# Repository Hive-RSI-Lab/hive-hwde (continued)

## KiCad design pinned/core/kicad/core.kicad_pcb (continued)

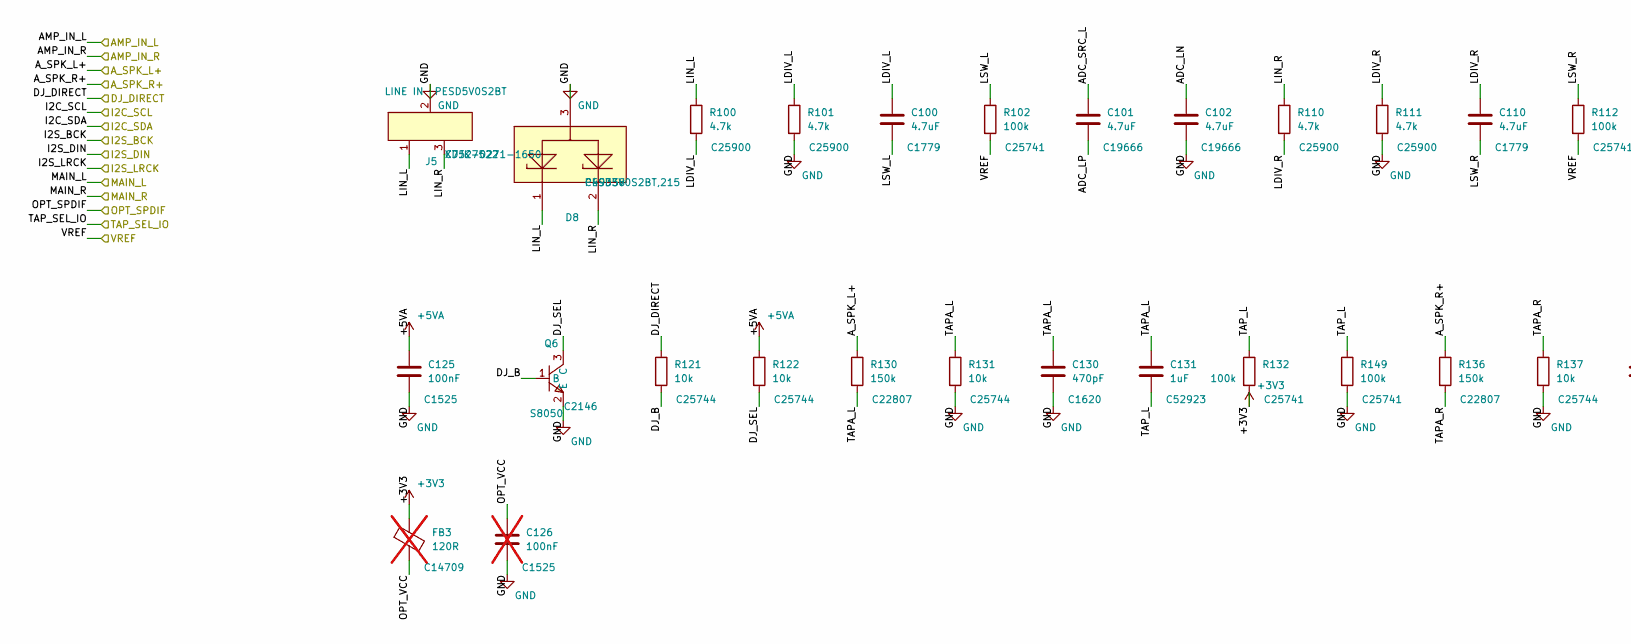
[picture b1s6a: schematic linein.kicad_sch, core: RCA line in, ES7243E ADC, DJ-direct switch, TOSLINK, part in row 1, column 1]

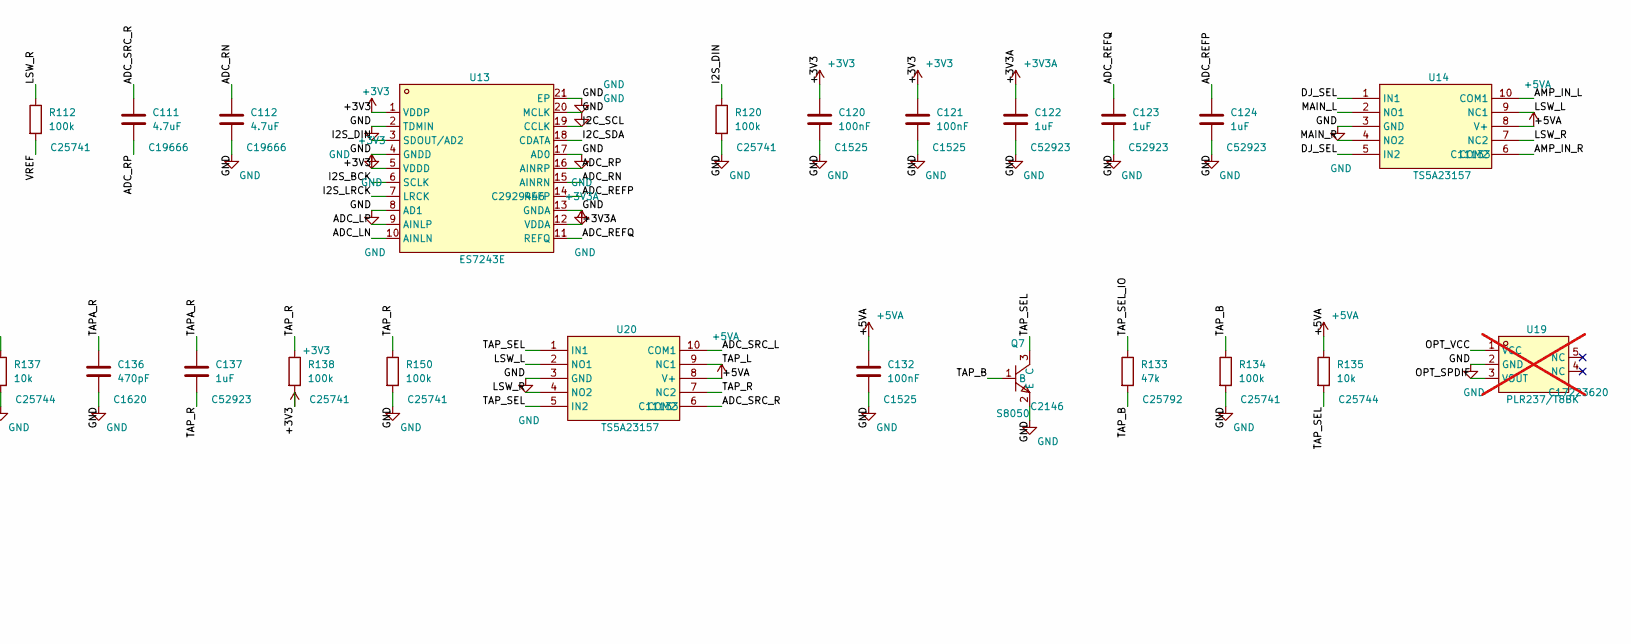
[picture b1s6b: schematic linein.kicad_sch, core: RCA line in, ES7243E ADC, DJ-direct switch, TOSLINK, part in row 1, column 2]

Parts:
C100, C110: 4.7uF; C0805; LCSC C1779
C101, C102, C111, C112: 4.7uF; C0603; LCSC C19666
C120, C121, C125, C132: 100nF; C0402; LCSC C1525
C122, C123, C124, C131, C137: 1uF; C0402; LCSC C52923
C126: 100nF; C0402; LCSC C1525; not fitted
C130, C136: 470pF; C0603; LCSC C1620
D8: PESD5V0S2BT; SOT-23_L2.9-W1.3-P1.90-LS2.4-BR; MPN PESD5V0S2BT,215; LCSC C49338
FB3: 120R; L0603; LCSC C14709; not fitted
J5: LINE IN; CONN-TH_XDJK-0271-1650; MPN XDJK-0271-1650; LCSC C7527522
Q6, Q7: S8050; SOT-23-3_L3.0-W1.7-P0.95-LS2.9-BR; LCSC C2146
R100, R101, R110, R111: 4.7k; R0402; LCSC C25900
R102, R112, R120, R132, R134, R138, R149, R150: 100k; R0402; LCSC C25741
R121, R122, R131, R135, R137: 10k; R0402; LCSC C25744
R130, R136: 150k; R0603; LCSC C22807
R133: 47k; R0402; LCSC C25792
U13: ES7243E; QFN-20_L3.0-W3.0-P0.40-BL-EP1.7; LCSC C2929446
U14, U20: TS5A23157; MSOP-10_L3.0-W3.0-P0.50-LS5.0-BL; LCSC C11133
U19: PLR237/T8BK; OPTO-TH_PLR237-T10BK; LCSC C17223620; not fitted

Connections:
+3V3: C120.1, C121.1, FB3.1, R132.2, R138.2, U13.1 (VDDP), U13.5 (VDDD); also elsewhere on the board
+3V3A: C122.1, U13.12 (VDDA); also elsewhere on the board
+5VA: C125.1, C132.1, R122.1, R135.1, U14.8 (V+), U20.8 (V+); also elsewhere on the board
/AMP_IN_L: U14.10 (COM1); also elsewhere on the board
/AMP_IN_R: U14.6 (COM2); also elsewhere on the board
/A_SPK_L+: R130.1; also elsewhere on the board
/A_SPK_R+: R136.1; also elsewhere on the board
/DJ_DIRECT: R121.1; also elsewhere on the board
/I2C_SCL: U13.19 (CCLK); also elsewhere on the board
/I2C_SDA: U13.18 (CDATA); also elsewhere on the board
/I2S_BCK: U13.6 (SCLK); also elsewhere on the board
/I2S_DIN: R120.1, U13.3 (SDOUT/AD2); also elsewhere on the board
/I2S_LRCK: U13.7 (LRCK); also elsewhere on the board
/MAIN_L: U14.2 (NO1); also elsewhere on the board
/MAIN_R: U14.4 (NO2); also elsewhere on the board
/OPT_SPDIF: U19.3 (VOUT); also elsewhere on the board
/TAP_SEL_IO: R133.1; also elsewhere on the board
/VREF: R102.2, R112.2; also elsewhere on the board
/linein/ADC_LN: C102.1, U13.10 (AINLN)
/linein/ADC_LP: C101.2, U13.9 (AINLP)
/linein/ADC_REFP: C124.1, U13.14 (REFP)
/linein/ADC_REFQ: C123.1, U13.11 (REFQ)
/linein/ADC_RN: C112.1, U13.15 (AINRN)
/linein/ADC_RP: C111.2, U13.16 (AINRP)
/linein/ADC_SRC_L: C101.1, U20.10 (COM1)
/linein/ADC_SRC_R: C111.1, U20.6 (COM2)
/linein/DJ_B: Q6.1 (B), R121.2
/linein/DJ_SEL: Q6.3 (C), R122.2, U14.1 (IN1), U14.5 (IN2)
/linein/LDIV_L: C100.1, R100.2, R101.1
/linein/LDIV_R: C110.1, R110.2, R111.1
/linein/LIN_L: D8.1, J5.1, R100.1
/linein/LIN_R: D8.2, J5.3, R110.1
/linein/LSW_L: C100.2, R102.1, U14.9 (NC1), U20.2 (NO1)
/linein/LSW_R: C110.2, R112.1, U14.7 (NC2), U20.4 (NO2)
/linein/OPT_VCC: C126.1, FB3.2, U19.1 (VCC)
/linein/TAPA_L: C130.1, C131.1, R130.2, R131.1
/linein/TAPA_R: C136.1, C137.1, R136.2, R137.1
/linein/TAP_B: Q7.1 (B), R133.2, R134.1
/linein/TAP_L: C131.2, R132.1, R149.1, U20.9 (NC1)
/linein/TAP_R: C137.2, R138.1, R150.1, U20.7 (NC2)
/linein/TAP_SEL: Q7.3 (C), R135.2, U20.1 (IN1), U20.5 (IN2)
GND: C102.2, C112.2, C120.2, C121.2, C122.2, C123.2, C124.2, C125.2, C126.2, C130.2, C132.2, C136.2, D8.3, J5.2, Q6.2 (E), Q7.2 (E), R101.2, R111.2, R120.2, R131.2, R134.2, R137.2, R149.2, R150.2, U13.2 (TDMIN), U13.4 (GNDD), U13.8 (AD1), U13.13 (GNDA), U13.17 (AD0), U13.20 (MCLK), U13.21 (EP), U14.3 (GND), U19.2 (GND), U20.3 (GND); also elsewhere on the board

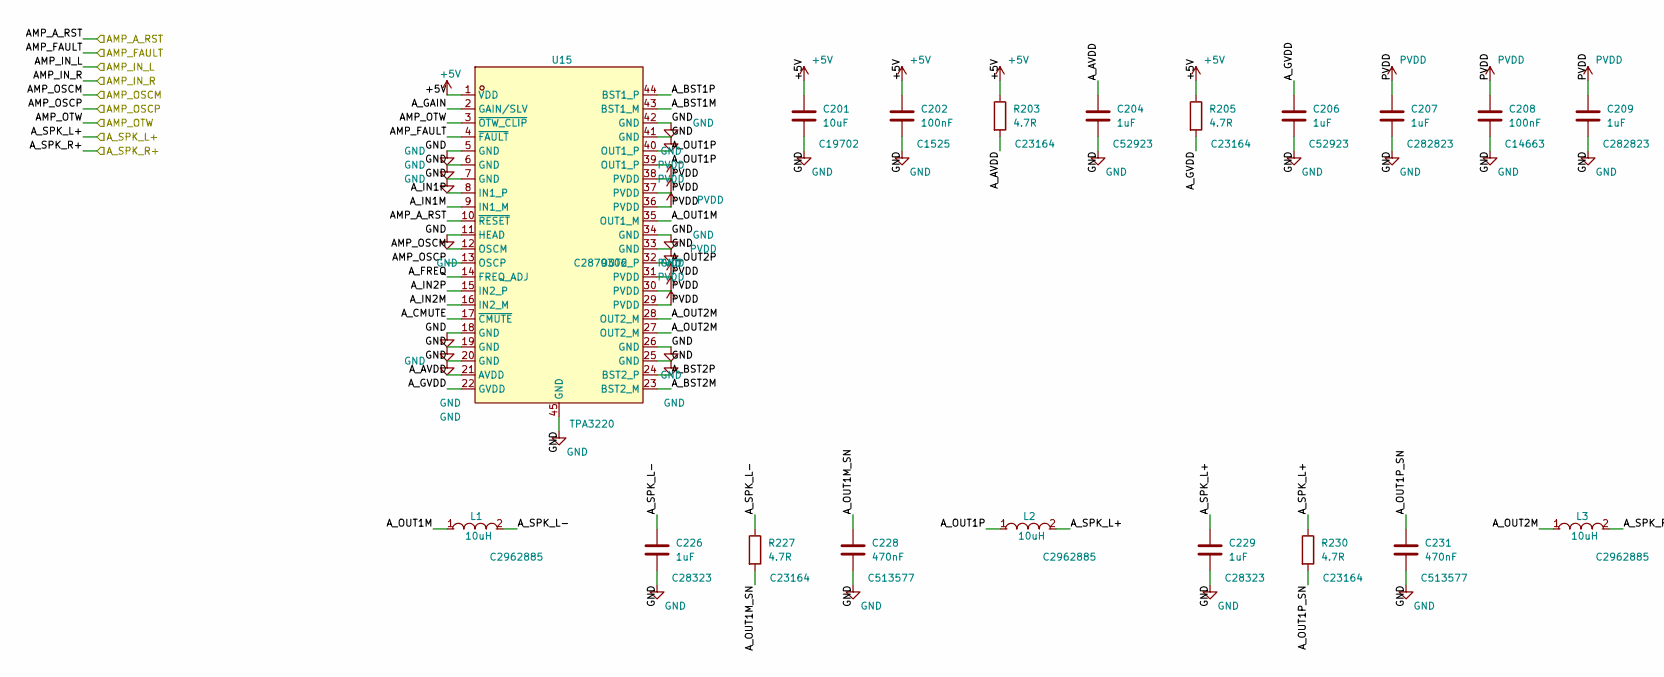
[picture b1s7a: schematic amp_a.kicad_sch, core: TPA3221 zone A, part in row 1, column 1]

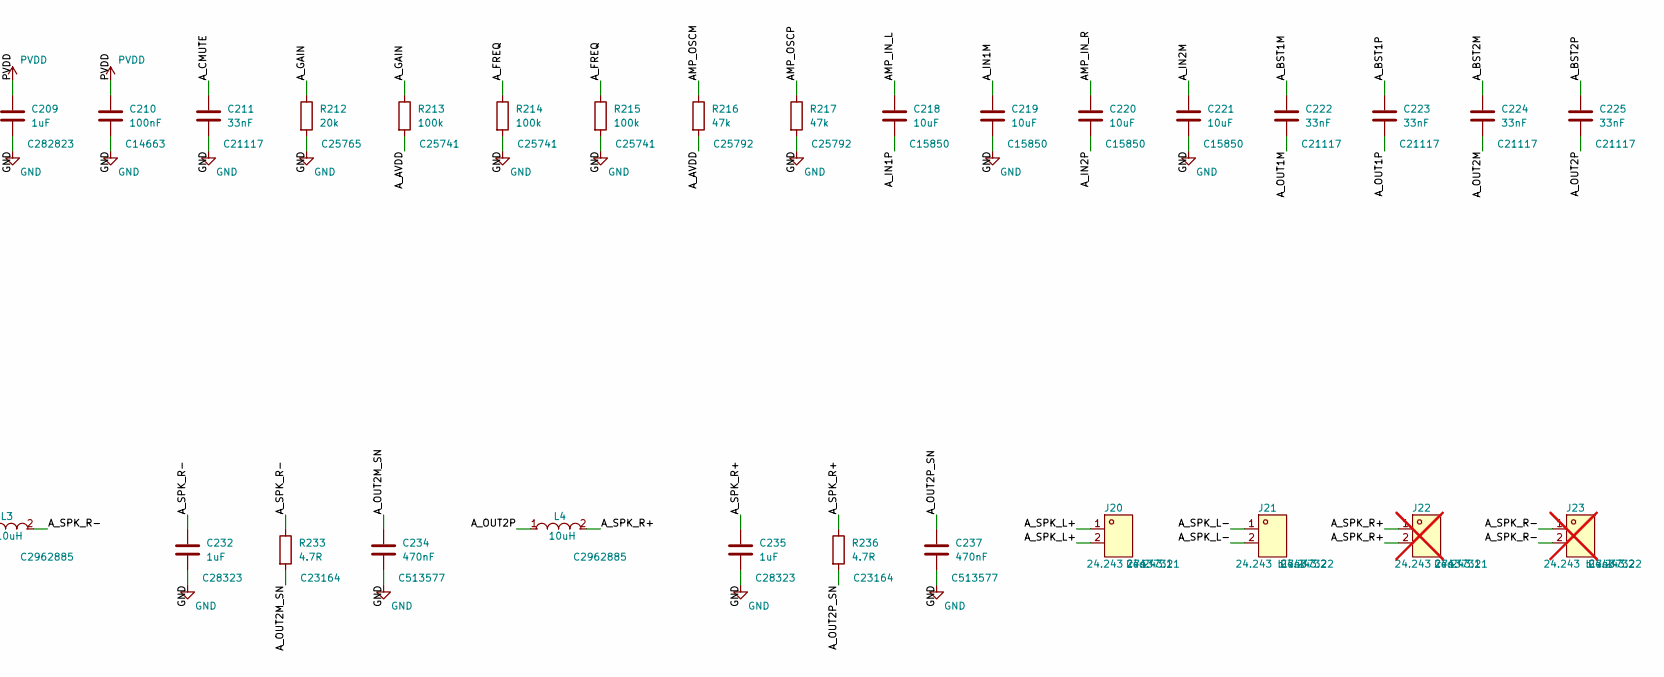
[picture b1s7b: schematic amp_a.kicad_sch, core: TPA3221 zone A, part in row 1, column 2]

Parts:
C201: 10uF; C0603; LCSC C19702
C202: 100nF; C0402; LCSC C1525
C204, C206: 1uF; C0402; LCSC C52923
C207, C209: 1uF; C1206; LCSC C282823
C208, C210: 100nF; C0603; LCSC C14663
C211, C222, C223, C224, C225: 33nF; C0603; LCSC C21117
C218, C219, C220, C221: 10uF; C0805; LCSC C15850
C226, C229, C232, C235: 1uF; C0805; LCSC C28323
C228, C231, C234, C237: 470nF; C0603; LCSC C513577
J20: 24.243 red; CONN-TH_24.243.1_RED; MPN 24.243.1; LCSC C7437321
J21: 24.243 black; CONN-TH_24.243.2; MPN 24.243.2; LCSC C7437322
J22: 24.243 red; CONN-TH_24.243.1_RED; MPN 24.243.1; LCSC C7437321; not fitted
J23: 24.243 black; CONN-TH_24.243.2; MPN 24.243.2; LCSC C7437322; not fitted
L1, L2, L3, L4: 10uH; IND-SMD_L8.5-W8.0_PCC-M0854M; LCSC C2962885
R203, R205, R227, R230, R233, R236: 4.7R; R0603; LCSC C23164
R212: 20k; R0402; LCSC C25765
R213, R214, R215: 100k; R0402; LCSC C25741
R216, R217: 47k; R0402; LCSC C25792
U15: TPA3220; HTSSOP-44-1EP_L14.0-W6.1-P0.64-LS8.1-EP7.3x4.43; LCSC C2879306

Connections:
+5V: C201.1, C202.1, R203.1, R205.1, U15.1 (VDD); also elsewhere on the board
/AMP_A_RST: U15.10 (~RESET); also elsewhere on the board
/AMP_FAULT: U15.4 (~FAULT); also elsewhere on the board
/AMP_IN_L: C218.1; also elsewhere on the board
/AMP_IN_R: C220.1; also elsewhere on the board
/AMP_OSCM: R216.1, U15.12 (OSCM); also elsewhere on the board
/AMP_OSCP: R217.1, U15.13 (OSCP); also elsewhere on the board
/AMP_OTW: U15.3 (~OTW_CLIP); also elsewhere on the board
/A_SPK_L+: C229.1, J20.1, J20.2, L2.2, R230.1; also elsewhere on the board
/A_SPK_R+: C235.1, J22.1, J22.2, L4.2, R236.1; also elsewhere on the board
/amp_a/A_AVDD: C204.1, R203.2, R213.2, R216.2, U15.21 (AVDD)
/amp_a/A_BST1M: C222.1, U15.43 (BST1_M)
/amp_a/A_BST1P: C223.1, U15.44 (BST1_P)
/amp_a/A_BST2M: C224.1, U15.23 (BST2_M)
/amp_a/A_BST2P: C225.1, U15.24 (BST2_P)
/amp_a/A_CMUTE: C211.1, U15.17 (~CMUTE)
/amp_a/A_FREQ: R214.1, R215.1, U15.14 (FREQ_ADJ)
/amp_a/A_GAIN: R212.1, R213.1, U15.2 (GAIN/SLV)
/amp_a/A_GVDD: C206.1, R205.2, U15.22 (GVDD)
/amp_a/A_IN1M: C219.1, U15.9 (IN1_M)
/amp_a/A_IN1P: C218.2, U15.8 (IN1_P)
/amp_a/A_IN2M: C221.1, U15.16 (IN2_M)
/amp_a/A_IN2P: C220.2, U15.15 (IN2_P)
/amp_a/A_OUT1M: C222.2, L1.1, U15.35 (OUT1_M)
/amp_a/A_OUT1M_SN: C228.1, R227.2
/amp_a/A_OUT1P: C223.2, L2.1, U15.39 (OUT1_P), U15.40 (OUT1_P)
/amp_a/A_OUT1P_SN: C231.1, R230.2
/amp_a/A_OUT2M: C224.2, L3.1, U15.27 (OUT2_M), U15.28 (OUT2_M)
/amp_a/A_OUT2M_SN: C234.1, R233.2
/amp_a/A_OUT2P: C225.2, L4.1, U15.32 (OUT2_P)
/amp_a/A_OUT2P_SN: C237.1, R236.2
/amp_a/A_SPK_L-: C226.1, J21.1, J21.2, L1.2, R227.1
/amp_a/A_SPK_R-: C232.1, J23.1, J23.2, L3.2, R233.1
GND: C201.2, C202.2, C204.2, C206.2, C207.2, C208.2, C209.2, C210.2, C211.2, C219.2, C221.2, C226.2, C228.2, C229.2, C231.2, C232.2, C234.2, C235.2, C237.2, R212.2, R214.2, R215.2, R217.2, U15.5 (GND), U15.6 (GND), U15.7 (GND), U15.11 (HEAD), U15.18 (GND), U15.19 (GND), U15.20 (GND), U15.25 (GND), U15.26 (GND), U15.33 (GND), U15.34 (GND), U15.41 (GND), U15.42 (GND), U15.45 (GND); also elsewhere on the board
PVDD: C207.1, C208.1, C209.1, C210.1, U15.29 (PVDD), U15.30 (PVDD), U15.31 (PVDD), U15.36 (PVDD), U15.37 (PVDD), U15.38 (PVDD); also elsewhere on the board

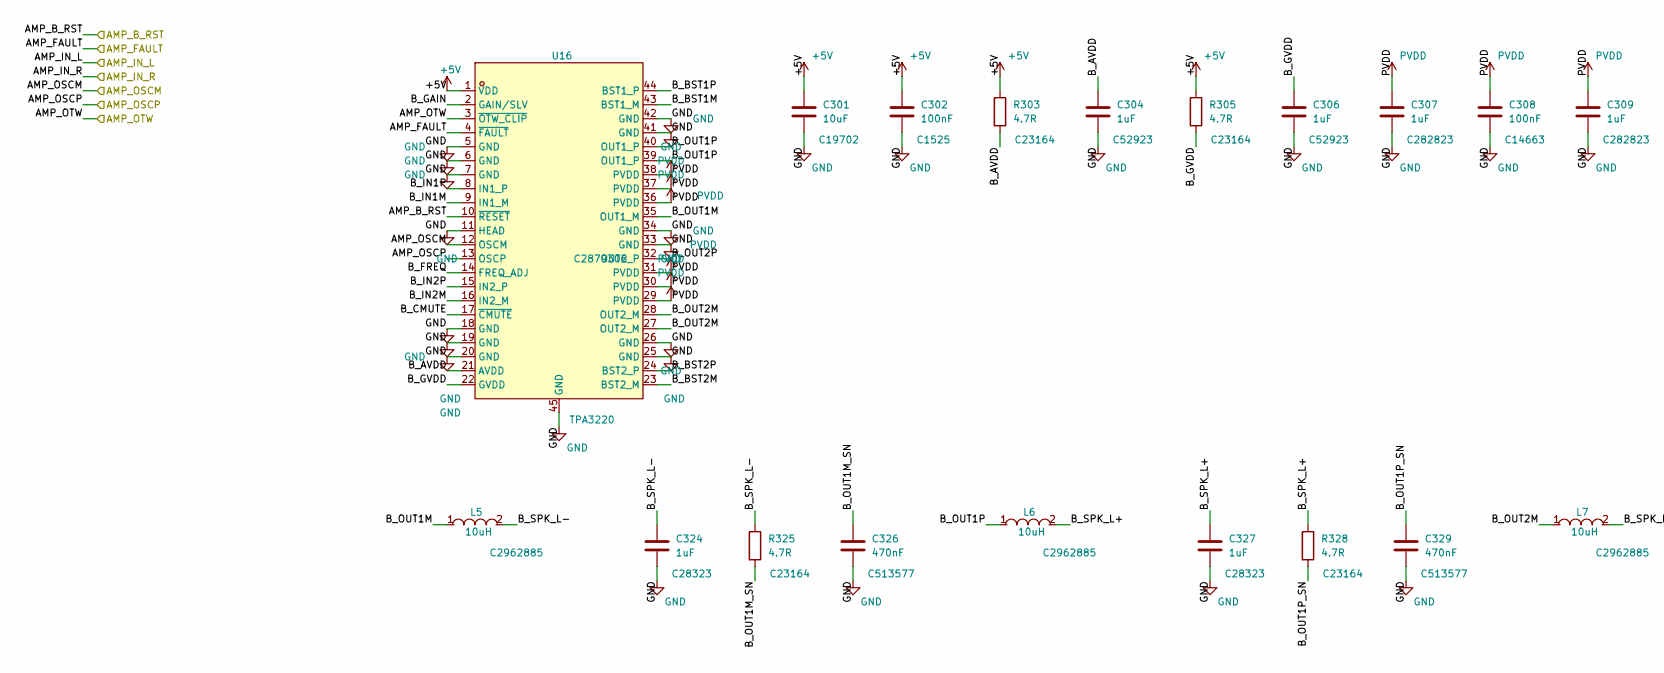
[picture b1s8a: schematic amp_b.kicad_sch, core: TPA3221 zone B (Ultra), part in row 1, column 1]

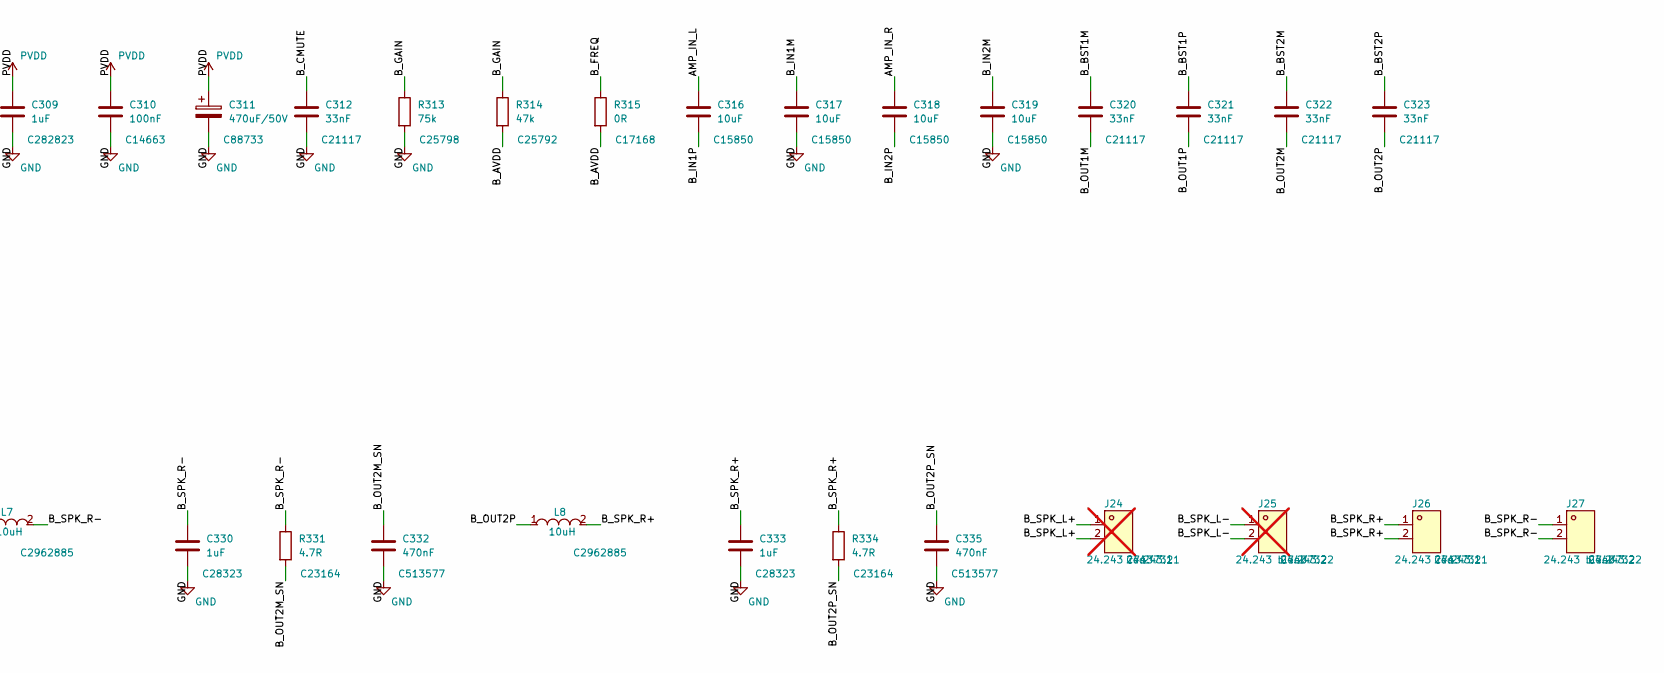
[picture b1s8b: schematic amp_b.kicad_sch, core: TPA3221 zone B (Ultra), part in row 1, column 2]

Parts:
C301: 10uF; C0603; LCSC C19702
C302: 100nF; C0402; LCSC C1525
C304, C306: 1uF; C0402; LCSC C52923
C307, C309: 1uF; C1206; LCSC C282823
C308, C310: 100nF; C0603; LCSC C14663
C311: 470uF/50V; CAP-TH_BD10.0-P5.00-D1.0-FD; LCSC C88733
C312, C320, C321, C322, C323: 33nF; C0603; LCSC C21117
C316, C317, C318, C319: 10uF; C0805; LCSC C15850
C324, C327, C330, C333: 1uF; C0805; LCSC C28323
C326, C329, C332, C335: 470nF; C0603; LCSC C513577
J24: 24.243 red; CONN-TH_24.243.1_RED; MPN 24.243.1; LCSC C7437321; not fitted
J25: 24.243 black; CONN-TH_24.243.2; MPN 24.243.2; LCSC C7437322; not fitted
J26: 24.243 red; CONN-TH_24.243.1_RED; MPN 24.243.1; LCSC C7437321
J27: 24.243 black; CONN-TH_24.243.2; MPN 24.243.2; LCSC C7437322
L5, L6, L7, L8: 10uH; IND-SMD_L8.5-W8.0_PCC-M0854M; LCSC C2962885
R303, R305, R325, R328, R331, R334: 4.7R; R0603; LCSC C23164
R313: 75k; R0402; LCSC C25798
R314: 47k; R0402; LCSC C25792
R315: 0R; R0402; LCSC C17168
U16: TPA3220; HTSSOP-44-1EP_L14.0-W6.1-P0.64-LS8.1-EP7.3x4.43; LCSC C2879306

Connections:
+5V: C301.1, C302.1, R303.1, R305.1, U16.1 (VDD); also elsewhere on the board
/AMP_B_RST: U16.10 (~RESET); also elsewhere on the board
/AMP_FAULT: U16.4 (~FAULT); also elsewhere on the board
/AMP_IN_L: C316.1; also elsewhere on the board
/AMP_IN_R: C318.1; also elsewhere on the board
/AMP_OSCM: U16.12 (OSCM); also elsewhere on the board
/AMP_OSCP: U16.13 (OSCP); also elsewhere on the board
/AMP_OTW: U16.3 (~OTW_CLIP); also elsewhere on the board
/amp_b/B_AVDD: C304.1, R303.2, R314.2, R315.2, U16.21 (AVDD)
/amp_b/B_BST1M: C320.1, U16.43 (BST1_M)
/amp_b/B_BST1P: C321.1, U16.44 (BST1_P)
/amp_b/B_BST2M: C322.1, U16.23 (BST2_M)
/amp_b/B_BST2P: C323.1, U16.24 (BST2_P)
/amp_b/B_CMUTE: C312.1, U16.17 (~CMUTE)
/amp_b/B_FREQ: R315.1, U16.14 (FREQ_ADJ)
/amp_b/B_GAIN: R313.1, R314.1, U16.2 (GAIN/SLV)
/amp_b/B_GVDD: C306.1, R305.2, U16.22 (GVDD)
/amp_b/B_IN1M: C317.1, U16.9 (IN1_M)
/amp_b/B_IN1P: C316.2, U16.8 (IN1_P)
/amp_b/B_IN2M: C319.1, U16.16 (IN2_M)
/amp_b/B_IN2P: C318.2, U16.15 (IN2_P)
/amp_b/B_OUT1M: C320.2, L5.1, U16.35 (OUT1_M)
/amp_b/B_OUT1M_SN: C326.1, R325.2
/amp_b/B_OUT1P: C321.2, L6.1, U16.39 (OUT1_P), U16.40 (OUT1_P)
/amp_b/B_OUT1P_SN: C329.1, R328.2
/amp_b/B_OUT2M: C322.2, L7.1, U16.27 (OUT2_M), U16.28 (OUT2_M)
/amp_b/B_OUT2M_SN: C332.1, R331.2
/amp_b/B_OUT2P: C323.2, L8.1, U16.32 (OUT2_P)
/amp_b/B_OUT2P_SN: C335.1, R334.2
/amp_b/B_SPK_L+: C327.1, J24.1, J24.2, L6.2, R328.1
/amp_b/B_SPK_L-: C324.1, J25.1, J25.2, L5.2, R325.1
/amp_b/B_SPK_R+: C333.1, J26.1, J26.2, L8.2, R334.1
/amp_b/B_SPK_R-: C330.1, J27.1, J27.2, L7.2, R331.1
GND: C301.2, C302.2, C304.2, C306.2, C307.2, C308.2, C309.2, C310.2, C311.2, C312.2, C317.2, C319.2, C324.2, C326.2, C327.2, C329.2, C330.2, C332.2, C333.2, C335.2, R313.2, U16.5 (GND), U16.6 (GND), U16.7 (GND), U16.11 (HEAD), U16.18 (GND), U16.19 (GND), U16.20 (GND), U16.25 (GND), U16.26 (GND), U16.33 (GND), U16.34 (GND), U16.41 (GND), U16.42 (GND), U16.45 (GND); also elsewhere on the board
PVDD: C307.1, C308.1, C309.1, C310.1, C311.1, U16.29 (PVDD), U16.30 (PVDD), U16.31 (PVDD), U16.36 (PVDD), U16.37 (PVDD), U16.38 (PVDD); also elsewhere on the board

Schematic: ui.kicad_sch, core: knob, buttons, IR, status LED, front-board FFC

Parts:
C400: 4.7uF; C0603; LCSC C19666
D3: KT-0603R; LED-SMD_L1.6-W0.8-R-RD; LCSC C2286
J3: FFC 20P; FPC-SMD_20P-P0.50_XUNPU_FPC-05F-20PH20; LCSC C2856803; not fitted
R400: 100R; R0402; LCSC C25076
R401: 470R; R0402; LCSC C25117
R402, R403: 33R; R0402; LCSC C25105; not fitted
SW1: EC11; SW-TH_EC11E1820402; LCSC C361165
SW2: BTN1; SW-SMD_4P-L5.1-W5.1-P3.70-LS6.5-TL_H1.5; MPN TS-1187A-B-A-B; LCSC C318884
SW3: BTN2; SW-SMD_4P-L5.1-W5.1-P3.70-LS6.5-TL_H1.5; MPN TS-1187A-B-A-B; LCSC C318884
U18: IRM-3638T; OPTO-TH_IRM-3638T; LCSC C42421366

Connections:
+3V3: J3.2, J3.19, R400.1; also elsewhere on the board
+5V: J3.3, J3.18; also elsewhere on the board
/BTN_1: SW2.1 (A), SW2.2 (B); also elsewhere on the board
/BTN_2: SW3.1 (A), SW3.2 (B); also elsewhere on the board
/ENC_A: J3.16, SW1.A; also elsewhere on the board
/ENC_B: J3.17, SW1.B; also elsewhere on the board
/ENC_SW: SW1.D; also elsewhere on the board
/EXP_INT: J3.14; also elsewhere on the board
/I2C_SCL: J3.12; also elsewhere on the board
/I2C_SDA: J3.13; also elsewhere on the board
/IR_IN: J3.15, U18.1 (OUT); also elsewhere on the board
/LCD_BL: J3.10; also elsewhere on the board
/LCD_CS: J3.8; also elsewhere on the board
/LCD_DC: J3.9; also elsewhere on the board
/LCD_MOSI: R403.1; also elsewhere on the board
/LCD_SCLK: R402.1; also elsewhere on the board
/LED_STATUS: R401.1; also elsewhere on the board
/ui/FFC_MOSI: J3.7, R403.2
/ui/FFC_SCK: J3.5, R402.2
/ui/IR_VCC: C400.1, R400.2, U18.3 (VCC)
/ui/LED_A: D3.1 (A), R401.2
GND: C400.2, D3.2 (K), J3.1, J3.4, J3.6, J3.11, J3.20, J3.21, J3.22, SW1.C, SW1.E, SW1.F, SW1.G, SW2.3 (C), SW2.4 (D), SW3.3 (C), SW3.4 (D), U18.2 (GND); also elsewhere on the board

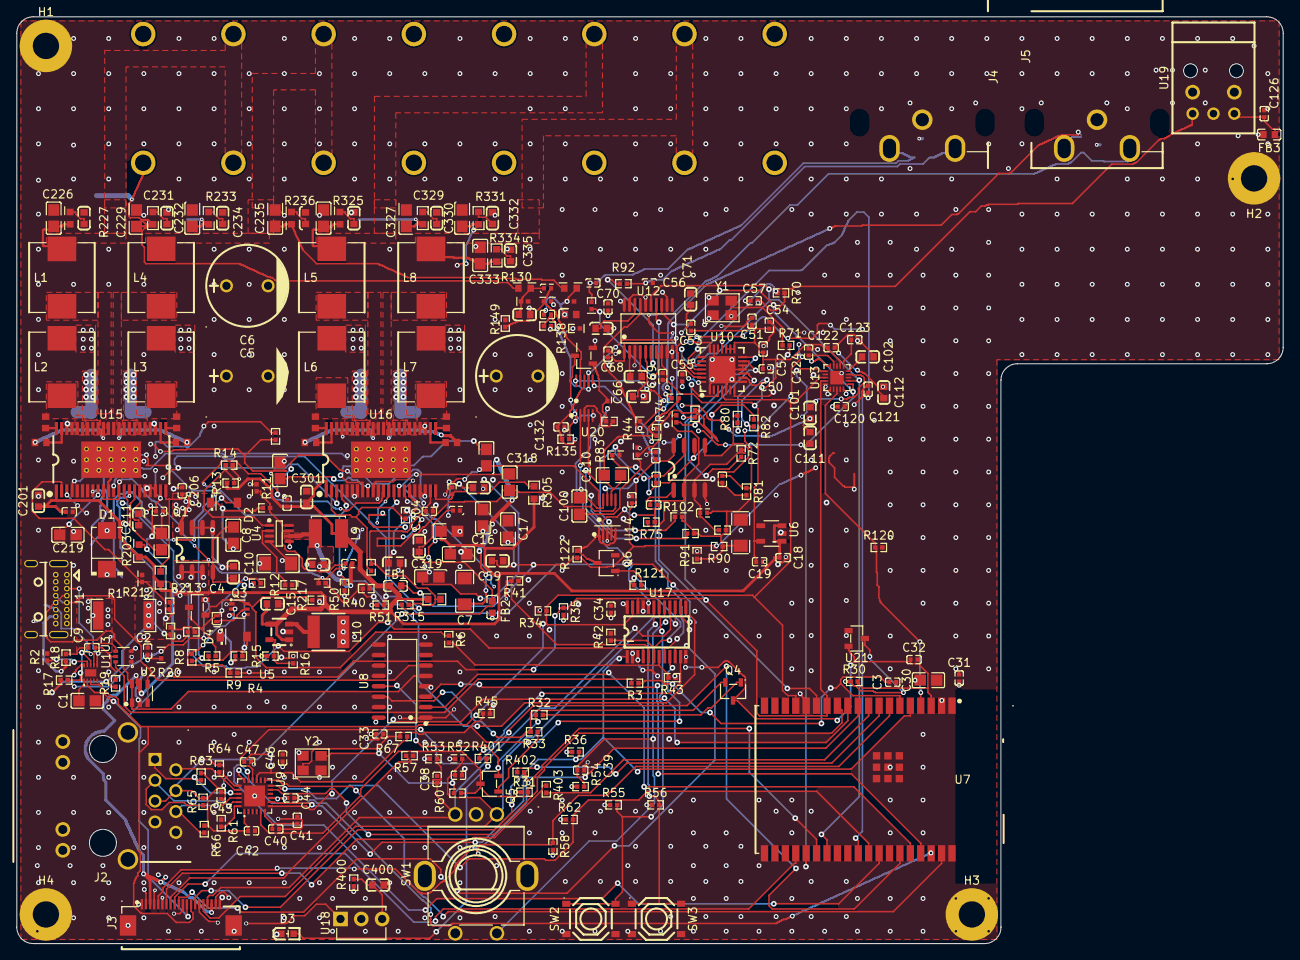
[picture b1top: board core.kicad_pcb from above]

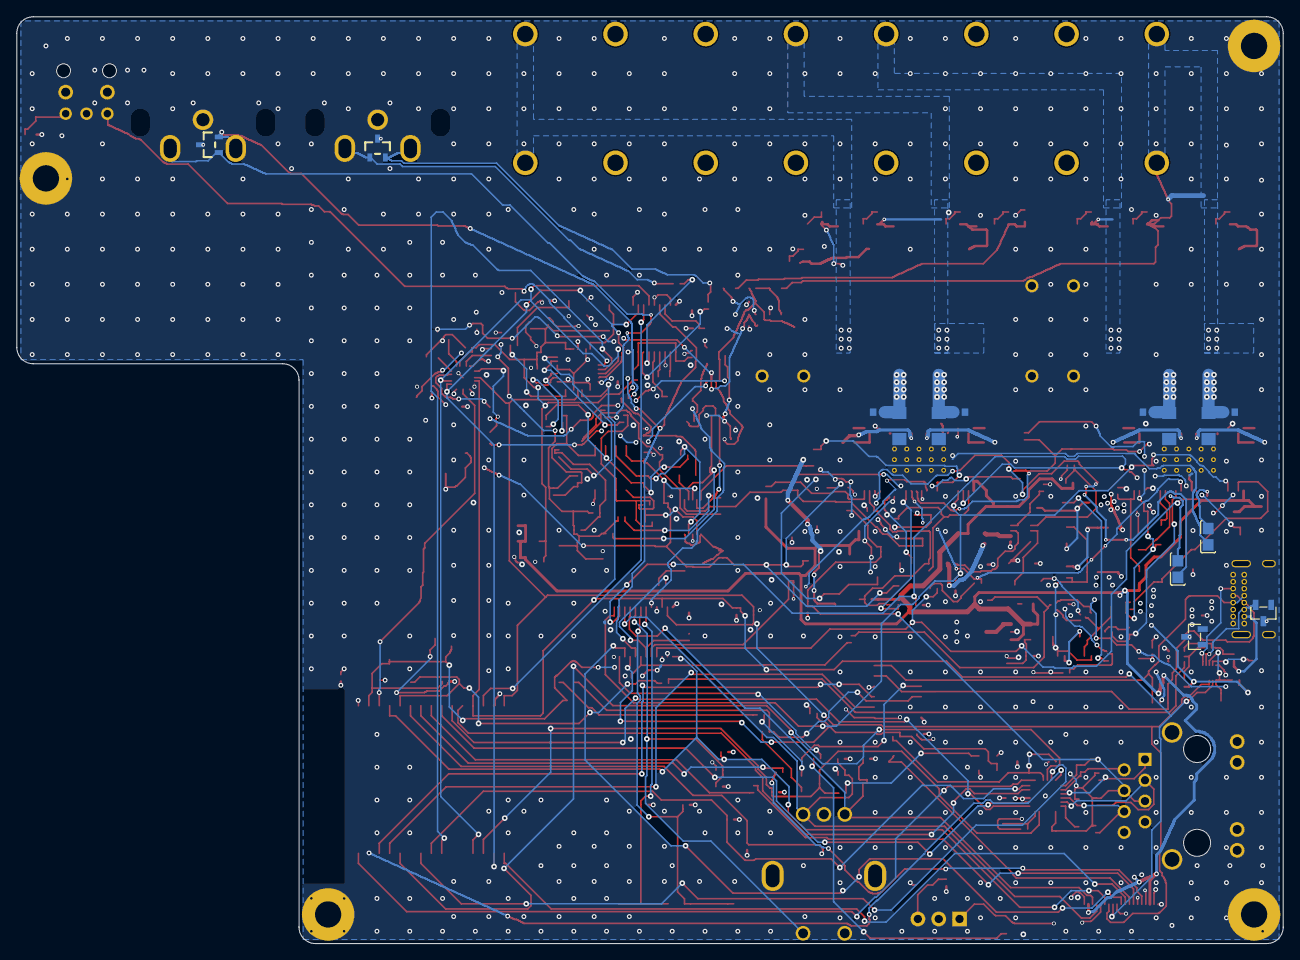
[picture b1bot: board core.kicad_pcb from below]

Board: 4 copper layers, 154.4 x 113.0 mm, 312 parts (14 on the bottom side), 190 nets.

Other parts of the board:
H1, H2, H3, H4: MountingHole_3.2mm_M3_Pad

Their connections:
GND: H1.1, H2.1, H3.1, H4.1; also elsewhere on the board
